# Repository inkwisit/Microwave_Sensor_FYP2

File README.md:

# Microwave_Sensor_FYP2
My final year project on subject of microwave sensors for industrial and robotics use. In an attempt to learn practical aspects of microwave theory, high frequency effects on circuit design, miniature radar and antennas we are recreating MIT Lincoln Lab synthetic aperture radar using own modules.

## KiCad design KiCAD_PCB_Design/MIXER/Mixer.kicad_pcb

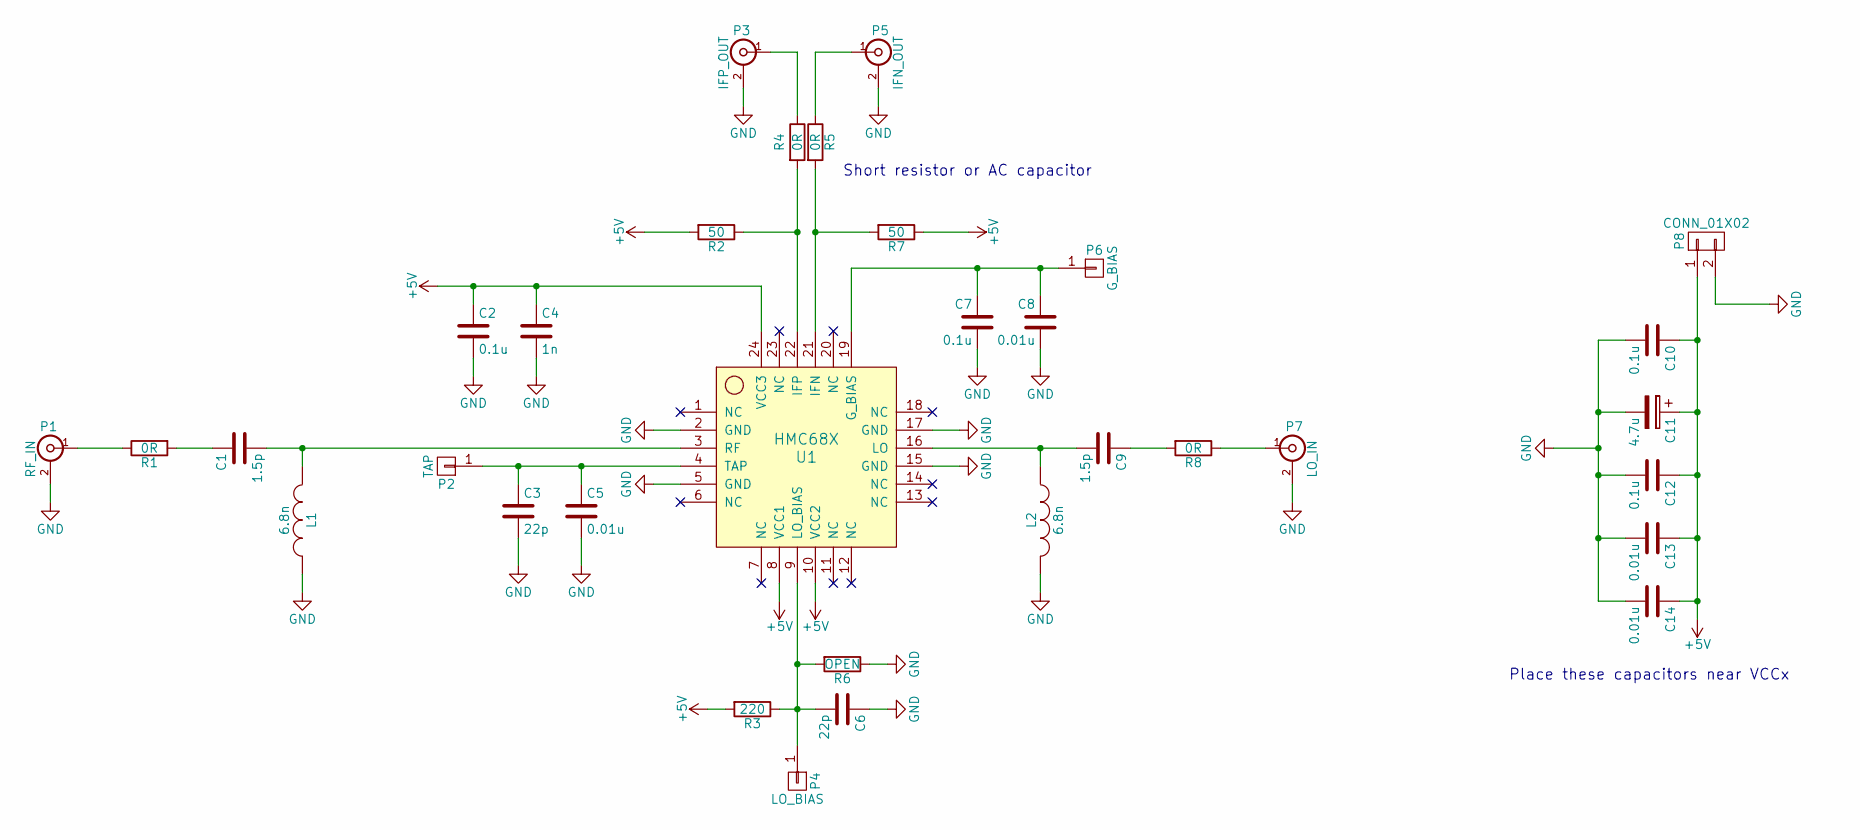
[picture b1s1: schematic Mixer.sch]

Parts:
C1, C9: 1.5p; C_0805_HandSoldering
C2, C7, C10, C12: 0.1u; C_0805_HandSoldering
C3, C6: 22p; C_0805_HandSoldering
C4: 1n; C_0805_HandSoldering
C5, C8, C13, C14: 0.01u; C_0805_HandSoldering
C11: 4.7u; TantalC_SizeA_EIA-3216_Reflow
L1, L2: 6.8n; R_0603_HandSoldering
P1: RF_IN; SMA
P2: TAP; Pin_Header_Straight_1x01
P3: IFP_OUT; SMA
P4: LO_BIAS; Pin_Header_Straight_1x01
P5: IFN_OUT; SMA
P6: G_BIAS; Pin_Header_Straight_1x01
P7: LO_IN; SMA
P8: CONN_01X02; Pin_Header_Straight_1x02
R1, R4, R5, R8: 0R; R_0805_HandSoldering
R2, R7: 50; R_0805_HandSoldering
R3: 220; R_0805_HandSoldering
R6: OPEN; R_0805_HandSoldering
U1: HMC68X; QFN-24-1EP_4x4mm_Pitch0.5mm

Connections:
+5V: C2.1, C4.1, C10.1, C11.1, C12.1, C13.1, C14.1, P8.1, R2.2, R3.2, R7.1, U1.8 (VCC1), U1.10 (VCC2), U1.24 (VCC3)
GND: C2.2, C3.2, C4.2, C5.2, C6.1, C7.2, C8.2, C10.2, C11.2, C12.2, C13.2, C14.2, L1.2, L2.2, P1.2 (Ext), P3.2 (Ext), P5.2 (Ext), P7.2 (Ext), P8.2, R6.1, U1.2 (GND), U1.5 (GND), U1.15 (GND), U1.17 (GND)
unnamed: C1.1, R1.2
unnamed: C1.2, L1.1, U1.3 (RF)
unnamed: C3.1, C5.1, P2.1, U1.4 (TAP)
unnamed: C6.2, P4.1, R3.1, R6.2, U1.9 (LO_BIAS)
unnamed: C7.1, C8.1, P6.1, U1.19 (G_BIAS)
unnamed: C9.1, R8.2
unnamed: C9.2, L2.1, U1.16 (LO)
unnamed: P1.1 (In), R1.1
unnamed: P3.1 (In), R4.1
unnamed: P5.1 (In), R5.1
unnamed: P7.1 (In), R8.1
unnamed: R2.1, R4.2, U1.22 (IFP)
unnamed: R5.2, R7.2, U1.21 (IFN)

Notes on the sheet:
Short resistor or AC capacitor
Place these capacitors near VCCx

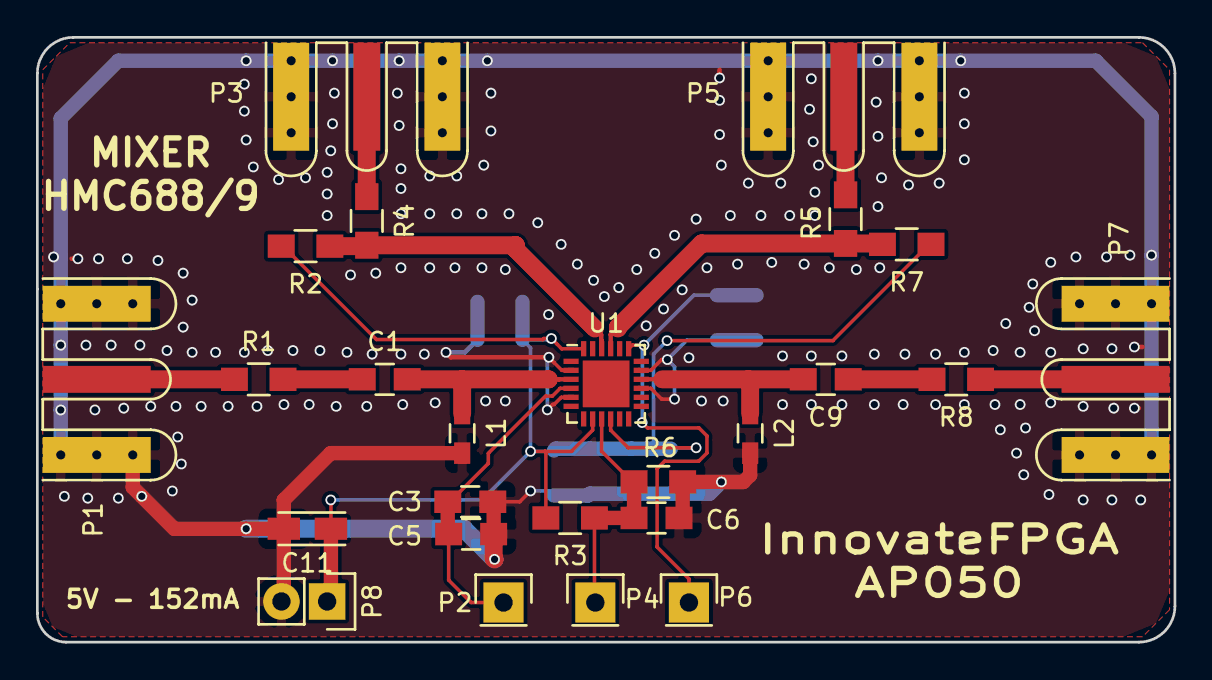
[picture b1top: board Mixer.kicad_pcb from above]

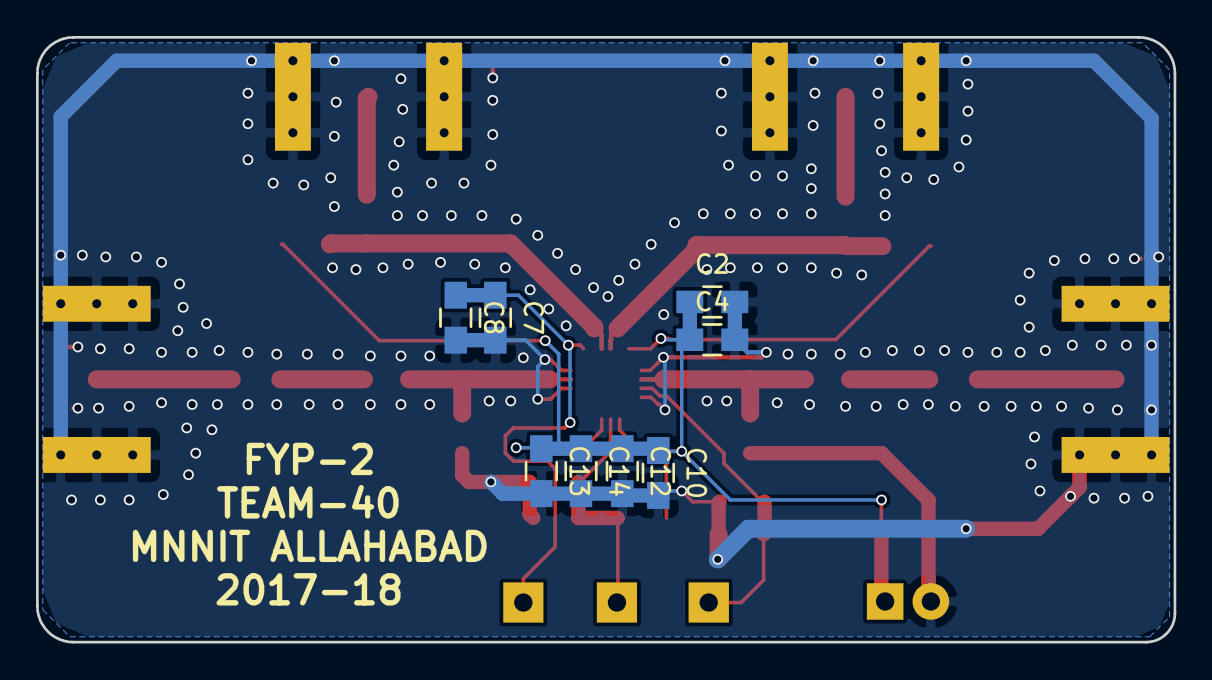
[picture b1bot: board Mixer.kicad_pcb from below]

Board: 2 copper layers, 63.2 x 33.6 mm, 33 parts (8 on the bottom side), 15 nets.

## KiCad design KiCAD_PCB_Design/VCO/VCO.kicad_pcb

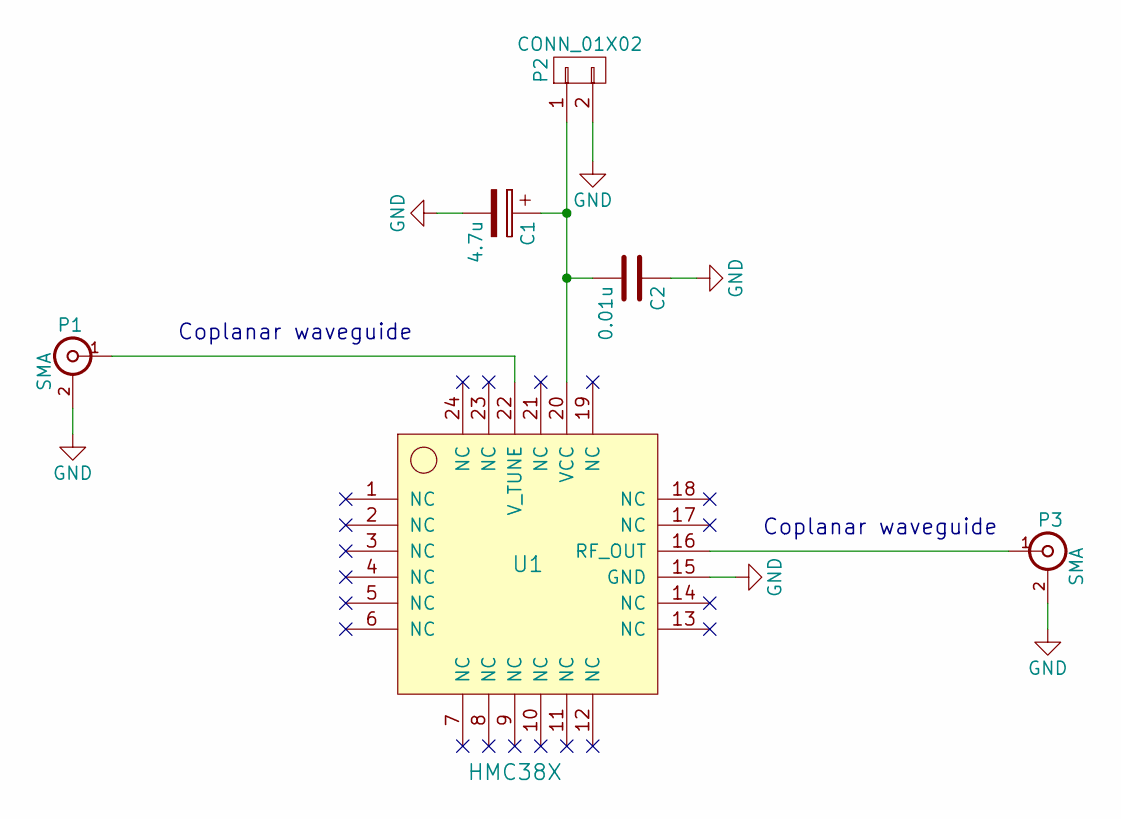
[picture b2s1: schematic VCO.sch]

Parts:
C1: 4.7u; TantalC_SizeA_EIA-3216_Wave
C2: 0.01u; C_0805_HandSoldering
P1, P3: SMA
P2: CONN_01X02; Pin_Header_Straight_1x02
U1: HMC38X; QFN-24-1EP_4x4mm_Pitch0.5mm

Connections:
GND: C1.2, C2.1, P1.2 (Ext), P2.2, P3.2 (Ext), U1.15 (GND)
unnamed: C1.1, C2.2, P2.1, U1.20 (VCC)
unnamed: P1.1 (In), U1.22 (V_TUNE)
unnamed: P3.1 (In), U1.16 (RF_OUT)

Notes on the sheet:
Coplanar waveguide

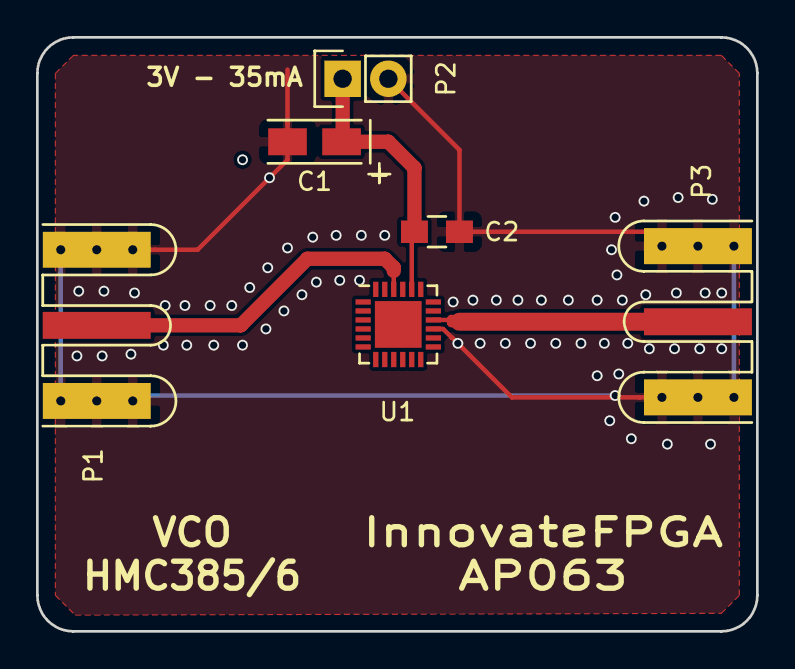
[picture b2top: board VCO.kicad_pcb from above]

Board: 2 copper layers, 40.0 x 33.0 mm, 6 parts (0 on the bottom side), 4 nets.

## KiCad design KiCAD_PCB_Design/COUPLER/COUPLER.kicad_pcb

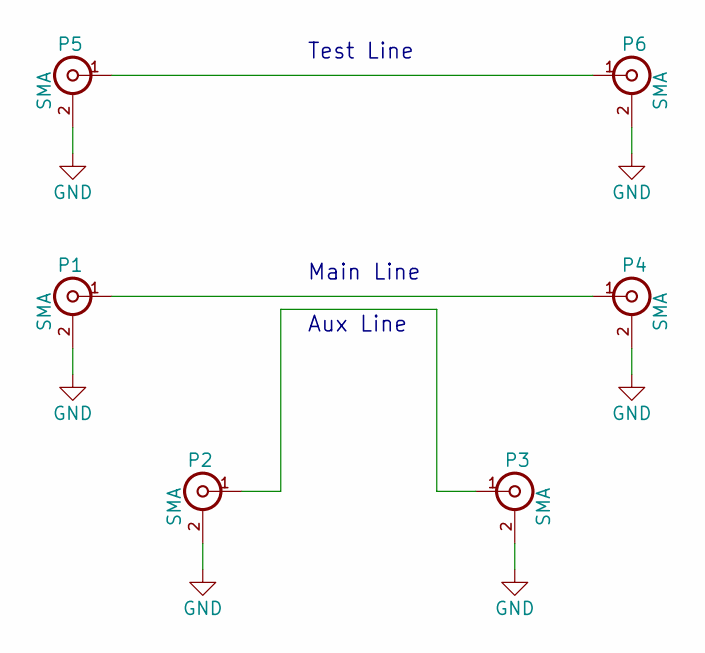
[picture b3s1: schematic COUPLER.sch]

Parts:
P1, P2, P3, P4, P5, P6: SMA

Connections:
GND: P1.2 (Ext), P2.2 (Ext), P3.2 (Ext), P4.2 (Ext), P5.2 (Ext), P6.2 (Ext)
unnamed: P1.1 (In), P4.1 (In)
unnamed: P2.1 (In), P3.1 (In)
unnamed: P5.1 (In), P6.1 (In)

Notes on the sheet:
Main Line
Aux Line
Test Line

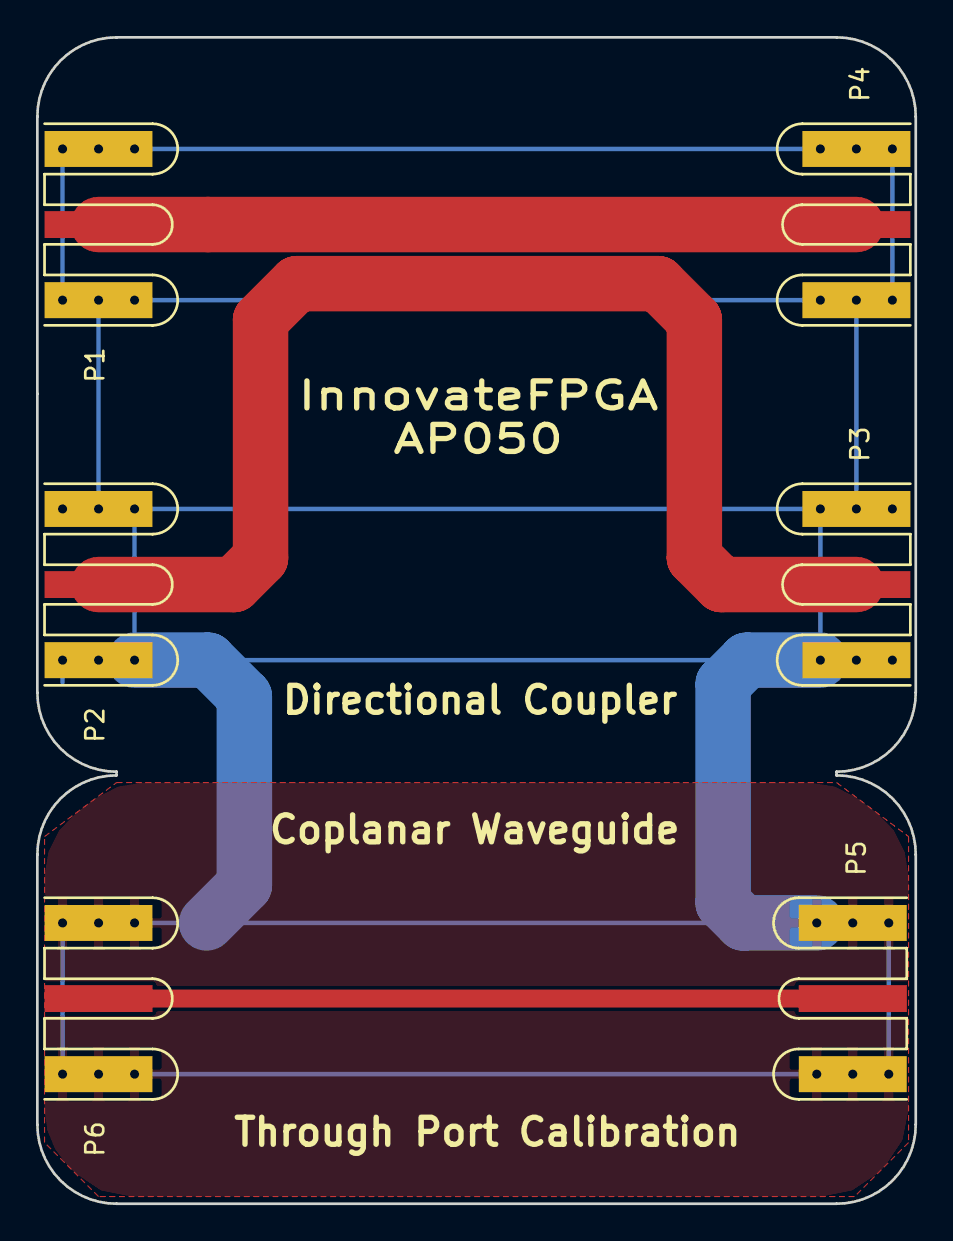
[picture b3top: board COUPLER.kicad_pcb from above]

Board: 2 copper layers, 48.8 x 64.8 mm, 6 parts (0 on the bottom side), 4 nets.

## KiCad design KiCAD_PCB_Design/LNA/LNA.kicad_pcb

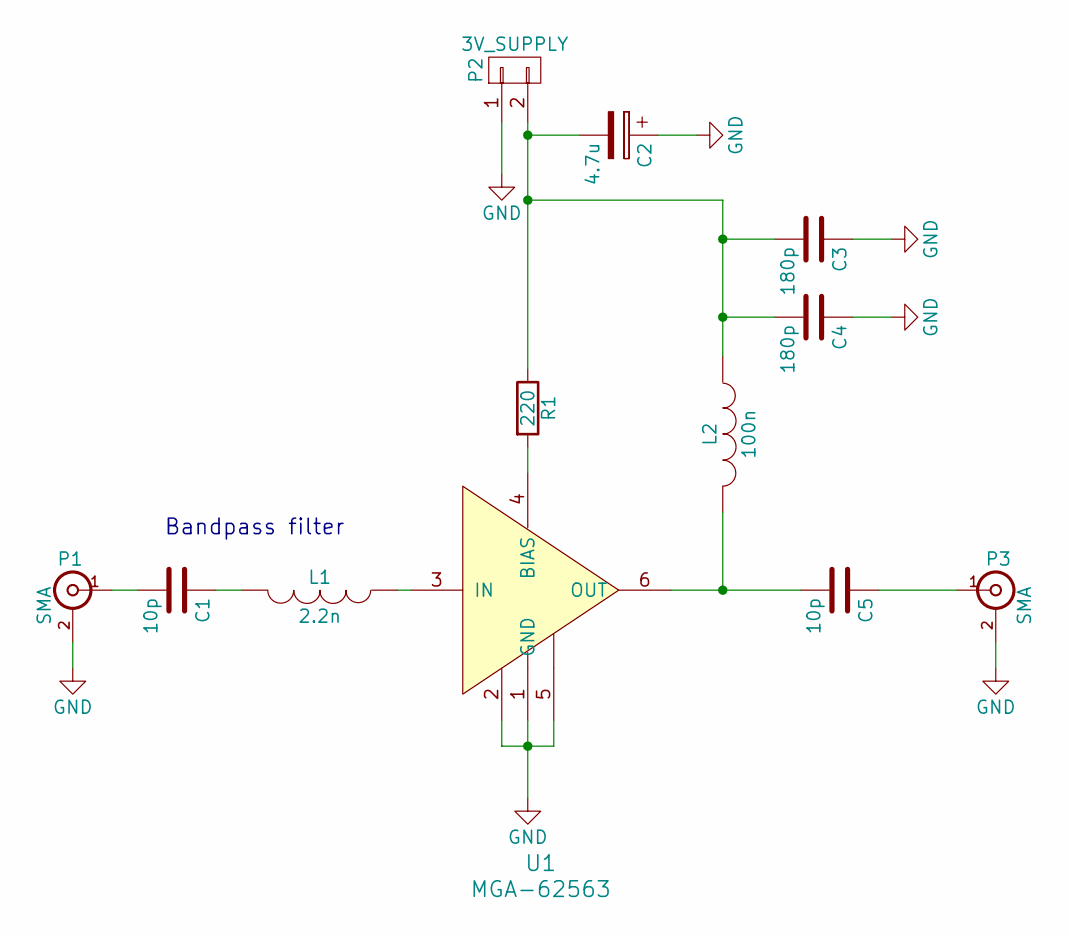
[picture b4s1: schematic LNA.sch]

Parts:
C1, C5: 10p; C_0805_HandSoldering
C2: 4.7u; TantalC_SizeA_EIA-3216_Wave
C3, C4: 180p; C_0805_HandSoldering
L1: 2.2n; R_0805_HandSoldering
L2: 100n; R_0805_HandSoldering
P1, P3: SMA
P2: 3V_SUPPLY; Pin_Header_Straight_1x02
R1: 220; R_0805_HandSoldering
U1: MGA-62563; SOT-363

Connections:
GND: C2.1, C3.1, C4.1, P1.2 (Ext), P2.1, P3.2 (Ext), U1.1 (GND), U1.2, U1.5
unnamed: C1.1, L1.2
unnamed: C1.2, P1.1 (In)
unnamed: C2.2, C3.2, C4.2, L2.1, P2.2, R1.1
unnamed: C5.1, P3.1 (In)
unnamed: C5.2, L2.2, U1.6 (OUT)
unnamed: L1.1, U1.3 (IN)
unnamed: R1.2, U1.4 (BIAS)

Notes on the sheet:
Bandpass filter

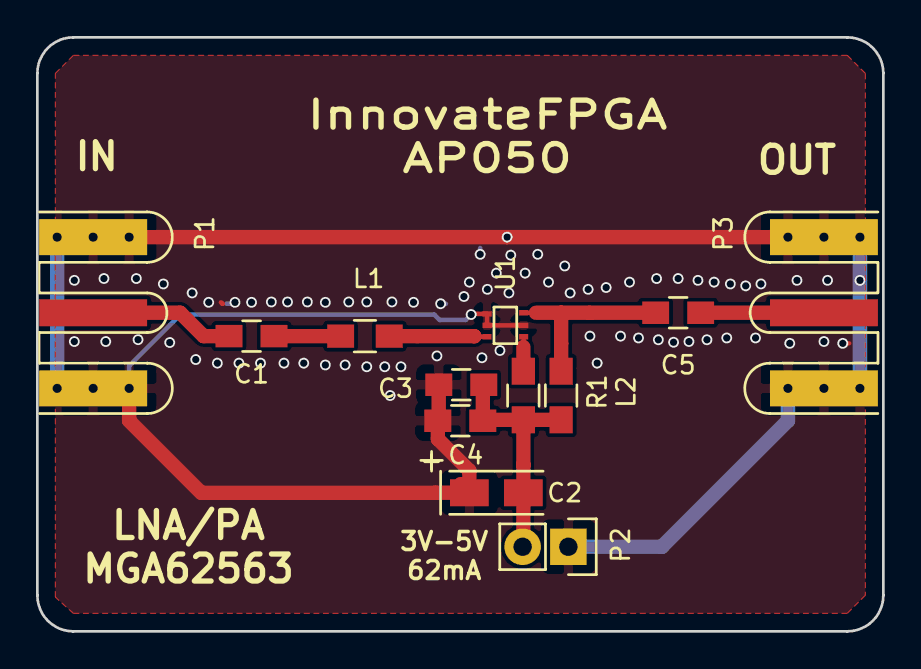
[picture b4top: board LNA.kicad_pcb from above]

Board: 2 copper layers, 47.0 x 33.0 mm, 12 parts (0 on the bottom side), 8 nets.

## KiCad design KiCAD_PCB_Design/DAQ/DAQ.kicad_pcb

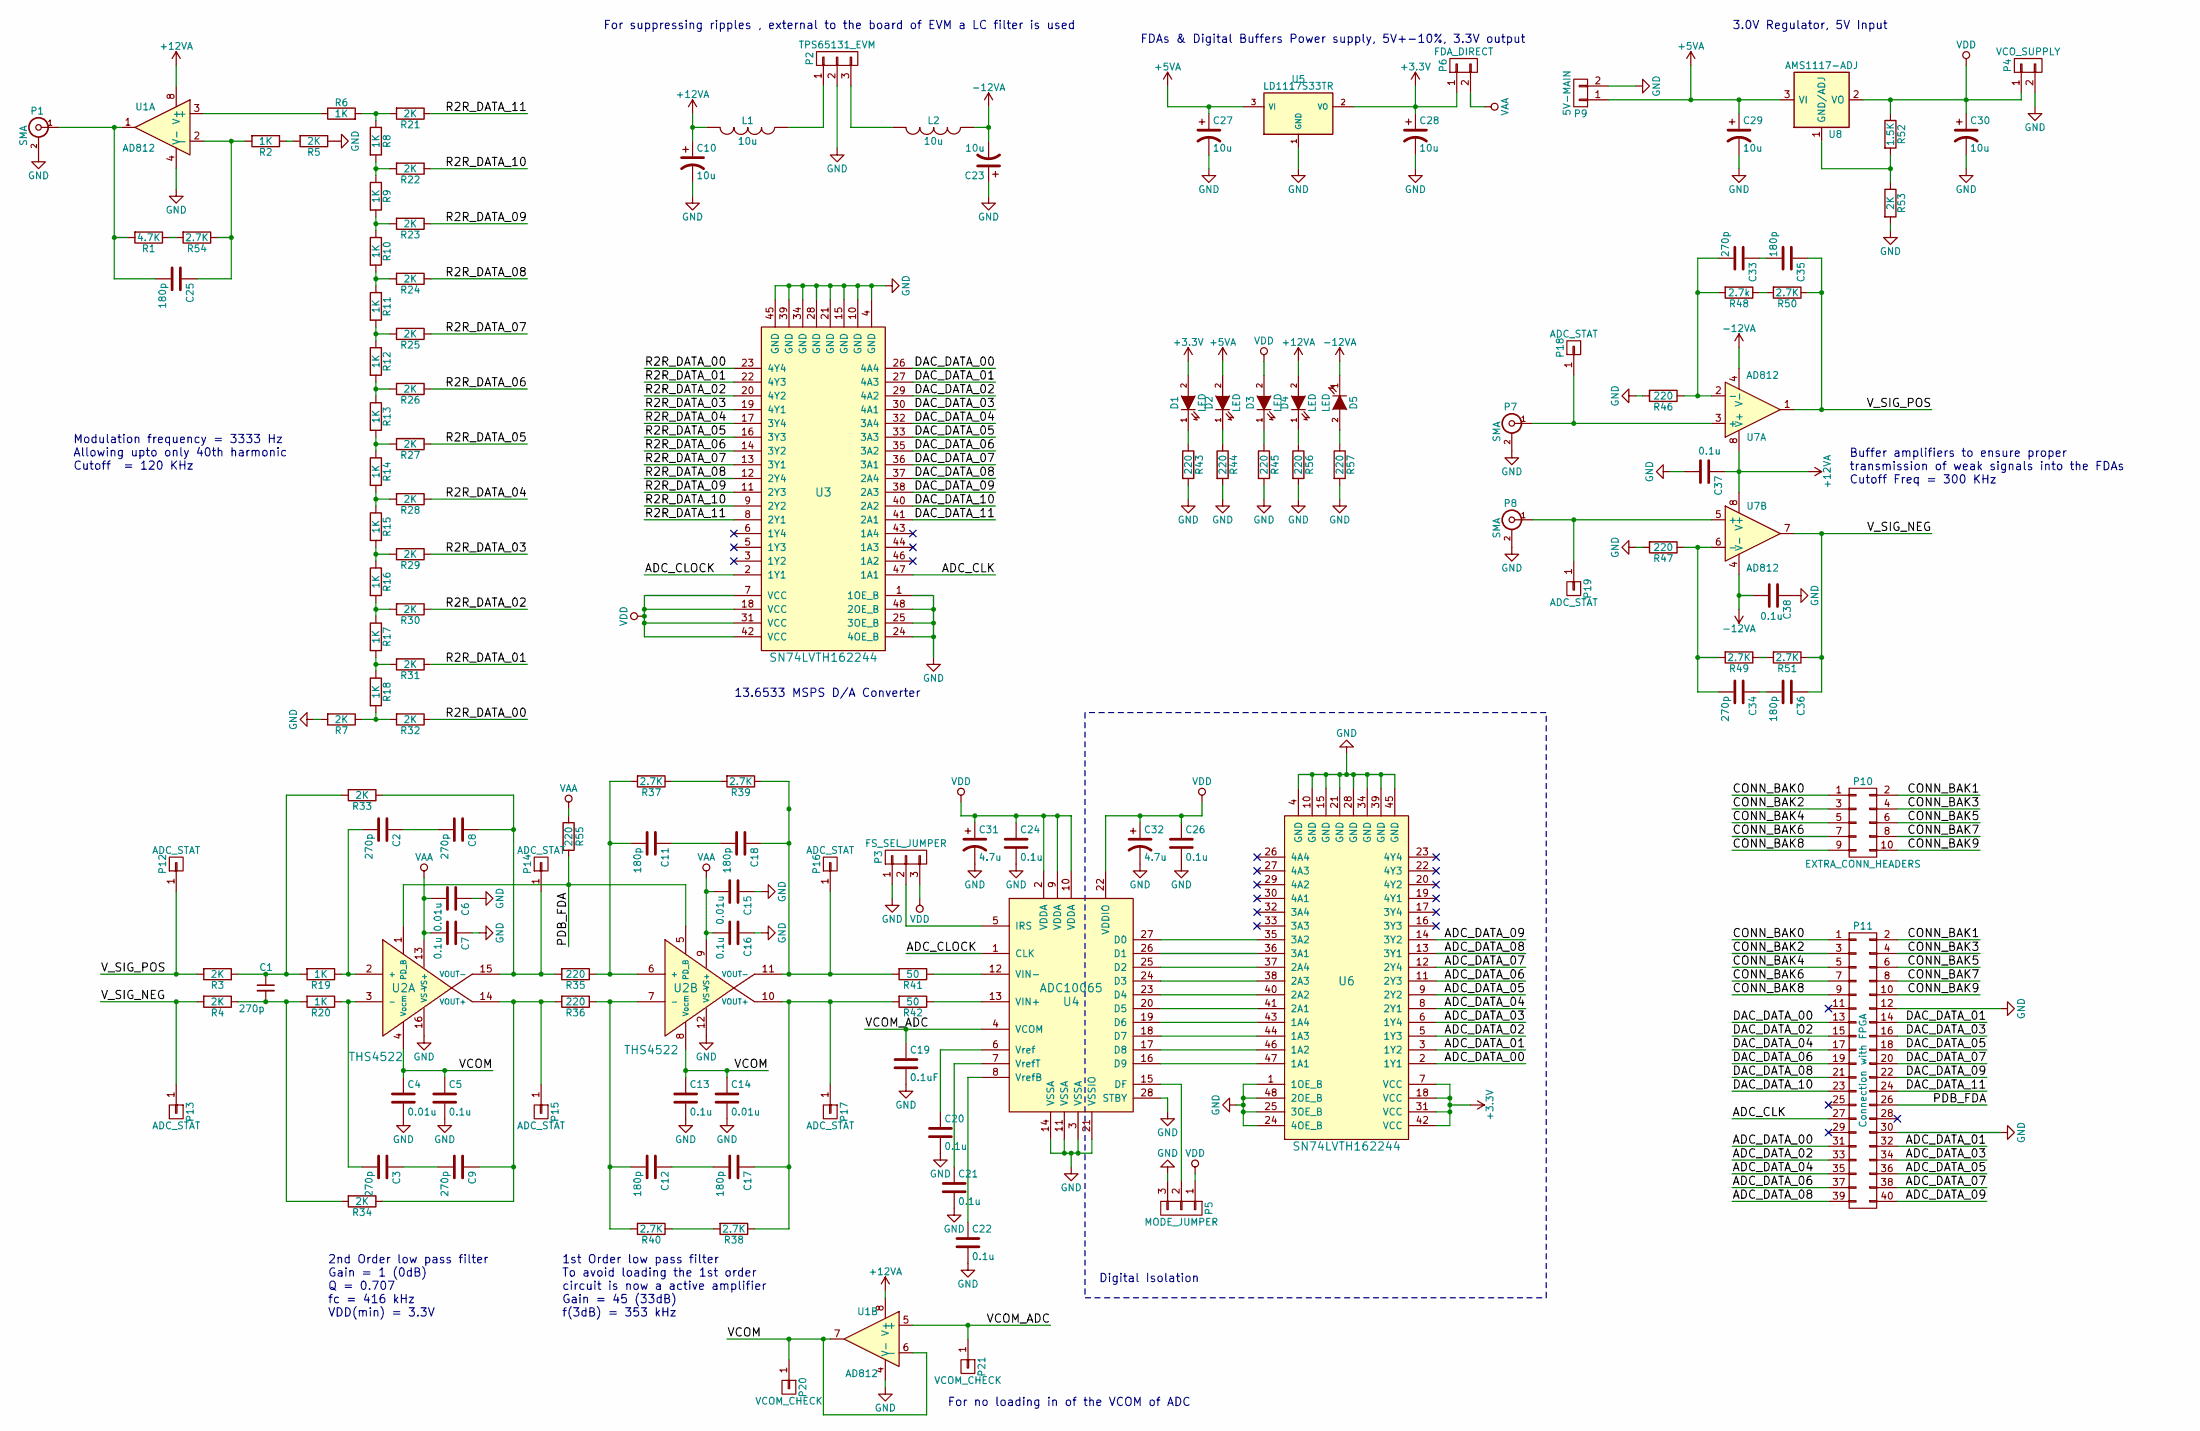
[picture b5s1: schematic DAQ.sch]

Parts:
C1, C2, C3, C8, C9, C33, C34: 270p; C_0805_HandSoldering
C4, C6, C14, C15: 0.01u; C_0805_HandSoldering
C5, C7, C13, C16, C20, C21, C22, C24, C26, C37, C38: 0.1u; C_0805_HandSoldering
C10, C23, C29, C30: 10u; c_elec_3x5.3
C11, C12, C17, C18, C25, C35, C36: 180p; C_0805_HandSoldering
C19: 0.1uF; C_0805_HandSoldering
C27, C28: 10u; TantalC_SizeS_EIA-3216
C31, C32: 4.7u; TantalC_SizeS_EIA-3216
D1, D2, D3, D4, D5: LED; LED_0805
L1, L2: 10u; Bourns_Semi_Shielded_Power_Inductor_SRN5040
P1, P7, P8: SMA
P2: TPS65131_EVM; Pin_Header_Straight_1x03
P3: FS_SEL_JUMPER; Pin_Header_Straight_1x03
P4: VCO_SUPPLY; Pin_Header_Straight_1x02
P5: MODE_JUMPER; Pin_Header_Straight_1x03
P6: FDA_DIRECT; Pin_Header_Straight_1x02
P9: 5V-MAIN; Pin_Header_Straight_1x02
P10: EXTRA_CONN_HEADERS; Pin_Header_Straight_2x05
P11: Connection with FPGA; Pin_Header_Straight_2x20
P12, P13, P14, P15, P16, P17, P18, P19: ADC_STAT; Pin_Header_Straight_1x01
P20, P21: VCOM_CHECK; Pin_Header_Straight_1x01
R1: 4.7K; R_0805_HandSoldering
R2, R6, R8, R9, R10, R11, R12, R13, R14, R15, R16, R17, R18, R19, R20: 1K; R_0805_HandSoldering
R3, R4, R5, R7, R21, R22, R23, R24, R25, R26, R27, R28, R29, R30, R31, R32, R33, R34, R53: 2K; R_0805_HandSoldering
R35, R36, R43, R44, R45, R46, R47, R55, R56, R57: 220; R_0805_HandSoldering
R37, R38, R39, R40, R49, R50, R51, R54: 2.7K; R_0805_HandSoldering
R41, R42: 50; R_0805_HandSoldering
R48: 2.7k; R_0805_HandSoldering
R52: 1.5K; R_0805_HandSoldering
U1, U7: AD812; SOIC-8_3.9x4.9mm_Pitch1.27mm
U2: THS4522; TSSOP-16_4.4x5mm_Pitch0.65mm
U3, U6: SN74LVTH162244; TSSOP-48_6.1x12.5mm_Pitch0.5mm
U4: ADC10065; TSSOP-28_4.4x9.7mm_Pitch0.65mm
U5: LD1117S33TR; SOT-223
U8: AMS1117-ADJ; SOT-223

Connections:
+3V3: C28.1, D1.2 (A), P6.1, U5.2 (VO), U6.7 (VCC), U6.18 (VCC), U6.31 (VCC), U6.42 (VCC)
+5VA: C27.1, C29.1, D2.2 (A), P9.1, U5.3 (VI), U8.3 (VI)
+12VA: C10.1, C37.1, D4.2 (A), L1.2, U1.8 (V+), U7.8 (V+)
-12VA: C23.2, C38.2, D5.1 (K), L2.1, U7.4 (V-)
/ADC_CLK: P11.27, U3.47 (1A1)
/ADC_CLOCK: U3.2 (1Y1), U4.1 (CLK)
/ADC_DATA_00: P11.31, U6.2 (1Y1)
/ADC_DATA_01: P11.32, U6.3 (1Y2)
/ADC_DATA_02: P11.33, U6.5 (1Y3)
/ADC_DATA_03: P11.34, U6.6 (1Y4)
/ADC_DATA_04: P11.35, U6.8 (2Y1)
/ADC_DATA_05: P11.36, U6.9 (2Y2)
/ADC_DATA_06: P11.37, U6.11 (2Y3)
/ADC_DATA_07: P11.38, U6.12 (2Y4)
/ADC_DATA_08: P11.39, U6.13 (3Y1)
/ADC_DATA_09: P11.40, U6.14 (3Y2)
/CONN_BAK0: P10.1, P11.1
/CONN_BAK1: P10.2, P11.2
/CONN_BAK2: P10.3, P11.3
/CONN_BAK3: P10.4, P11.4
/CONN_BAK4: P10.5, P11.5
/CONN_BAK5: P10.6, P11.6
/CONN_BAK6: P10.7, P11.7
/CONN_BAK7: P10.8, P11.8
/CONN_BAK8: P10.9, P11.9
/CONN_BAK9: P10.10, P11.10
/DAC_DATA_00: P11.13, U3.26 (4A4)
/DAC_DATA_01: P11.14, U3.27 (4A3)
/DAC_DATA_02: P11.15, U3.29 (4A2)
/DAC_DATA_03: P11.16, U3.30 (4A1)
/DAC_DATA_04: P11.17, U3.32 (3A4)
/DAC_DATA_05: P11.18, U3.33 (3A3)
/DAC_DATA_06: P11.19, U3.35 (3A2)
/DAC_DATA_07: P11.20, U3.36 (3A1)
/DAC_DATA_08: P11.21, U3.37 (2A4)
/DAC_DATA_09: P11.22, U3.38 (2A3)
/DAC_DATA_10: P11.23, U3.40 (2A2)
/DAC_DATA_11: P11.24, U3.41 (2A1)
/PDB_FDA: P11.26, R55.2, U2.1 (PD_B), U2.5 (PD_B)
/R2R_DATA_00: R32.1, U3.23 (4Y4)
/R2R_DATA_01: R31.1, U3.22 (4Y3)
/R2R_DATA_02: R30.1, U3.20 (4Y2)
/R2R_DATA_03: R29.1, U3.19 (4Y1)
/R2R_DATA_04: R28.1, U3.17 (3Y4)
/R2R_DATA_05: R27.1, U3.16 (3Y3)
/R2R_DATA_06: R26.1, U3.14 (3Y2)
/R2R_DATA_07: R25.1, U3.13 (3Y1)
/R2R_DATA_08: R24.1, U3.12 (2Y4)
/R2R_DATA_09: R23.1, U3.11 (2Y3)
/R2R_DATA_10: R22.1, U3.9 (2Y2)
/R2R_DATA_11: R21.1, U3.8 (2Y1)
/VCOM: C4.1, C5.1, C13.1, C14.1, P20.1, U1.6 (-), U1.7, U2.4 (Vocm), U2.8 (Vocm)
/VCOM_ADC: C19.1, P21.1, U1.5 (+), U4.4 (VCOM)
/V_SIG_NEG: C36.1, P13.1, R4.2, R51.1, U7.7
/V_SIG_POS: C35.1, P12.1, R3.2, R50.1, U7.1
GND: C4.2, C5.2, C6.1, C7.1, C10.2, C13.2, C14.2, C15.1, C16.1, C19.2, C20.2, C21.2, C22.2, C23.1, C24.2, C26.2, C27.2, C28.2, C29.2, C30.2, C31.2, C32.2, C37.2, C38.1, P1.2 (Ext), P2.2, P3.1, P4.2, P5.3, P7.2 (Ext), P8.2 (Ext), P9.2, P11.12, P11.30, R5.1, R7.2, R43.2, R44.2, R45.2, R46.2, R47.2, R53.2, R56.2, R57.2, U1.4 (V-), U2.12 (VS-), U2.16 (VS-), U3.1 (1OE_B), U3.4 (GND), U3.10 (GND), U3.15 (GND), U3.21 (GND), U3.24 (4OE_B), U3.25 (3OE_B), U3.28 (GND), U3.34 (GND), U3.39 (GND), U3.45 (GND), U3.48 (2OE_B), U4.3 (VSSA), U4.11 (VSSA), U4.14 (VSSA), U4.21 (VSSIO), U4.28 (STBY), U5.1 (GND), U6.1 (1OE_B), U6.4 (GND), U6.10 (GND), U6.15 (GND), U6.21 (GND), U6.24 (4OE_B), U6.25 (3OE_B), U6.28 (GND), U6.34 (GND), U6.39 (GND), U6.45 (GND), U6.48 (2OE_B)
unnamed: C1.1, R3.1, R19.2, R33.2
unnamed: C1.2, R4.1, R20.2, R34.2
unnamed: C2.1, C8.2
unnamed: C2.2, R19.1, U2.2 (+)
unnamed: C3.1, C9.2
unnamed: C3.2, R20.1, U2.3 (-)
unnamed: C8.1, P14.1, R33.1, R35.2, U2.15 (VOUT-)
unnamed: C9.1, P15.1, R34.1, R36.2, U2.14 (VOUT+)
unnamed: C11.1, C18.2
unnamed: C11.2, R35.1, R37.2, U2.6 (+)
unnamed: C12.1, C17.2
unnamed: C12.2, R36.1, R40.2, U2.7 (-)
unnamed: C17.1, P17.1, R38.1, R42.2, U2.10 (VOUT+)
unnamed: C18.1, P16.1, R39.1, R41.2, U2.11 (VOUT-)
unnamed: C20.1, U4.6 (Vref)
unnamed: C21.1, U4.7 (VrefT)
unnamed: C22.1, U4.8 (VrefB)
unnamed: C25.1, R2.2, R54.1, U1.2 (-)
unnamed: C25.2, P1.1 (In), R1.2, U1.1
unnamed: C33.1, C35.2
unnamed: C33.2, R46.1, R48.2, U7.2 (-)
unnamed: C34.1, C36.2
unnamed: C34.2, R47.1, R49.2, U7.6 (-)
unnamed: D1.1 (K), R43.1
unnamed: D2.1 (K), R44.1
unnamed: D3.1 (K), R45.1
unnamed: D4.1 (K), R56.1
unnamed: D5.2 (A), R57.1
unnamed: L1.1, P2.1
unnamed: L2.2, P2.3
unnamed: P3.2, U4.5 (IRS)
unnamed: P5.2, U4.15 (DF)
unnamed: P7.1 (In), P18.1, U7.3 (+)
unnamed: P8.1 (In), P19.1, U7.5 (+)
unnamed: R1.1, R54.2
unnamed: R2.1, R5.2
unnamed: R6.1, U1.3 (+)
unnamed: R9.2, R10.1, R23.2
unnamed: R10.2, R11.1, R24.2
unnamed: R11.2, R12.1, R25.2
unnamed: R12.2, R13.1, R26.2
unnamed: R13.2, R14.1, R27.2
unnamed: R14.2, R15.1, R28.2
unnamed: R15.2, R16.1, R29.2
unnamed: R16.2, R17.1, R30.2
unnamed: R17.2, R18.1, R31.2
unnamed: R7.1, R18.2, R32.2
unnamed: R6.2, R8.1, R21.2
unnamed: R8.2, R9.1, R22.2
unnamed: R37.1, R39.2
unnamed: R38.2, R40.1
unnamed: R41.1, U4.12 (VIN-)
unnamed: R42.1, U4.13 (VIN+)
unnamed: R48.1, R50.2
unnamed: R49.1, R51.2
unnamed: R52.2, R53.1, U8.1 (GND/ADJ)
unnamed: U4.16 (D9), U6.47 (1A1)
unnamed: U4.17 (D8), U6.46 (1A2)
unnamed: U4.18 (D7), U6.44 (1A3)
unnamed: U4.19 (D6), U6.43 (1A4)
unnamed: U4.20 (D5), U6.41 (2A1)
unnamed: U4.23 (D4), U6.40 (2A2)
unnamed: U4.24 (D3), U6.38 (2A3)
unnamed: U4.25 (D2), U6.37 (2A4)
unnamed: U4.26 (D1), U6.36 (3A1)
unnamed: U4.27 (D0), U6.35 (3A2)
VAA: C6.2, C7.2, C15.2, C16.2, P6.2, R55.1, U2.9 (VS+), U2.13 (VS+)
VDD: C24.1, C26.1, C30.1, C31.1, C32.1, D3.2 (A), P3.3, P4.1, P5.1, R52.1, U3.7 (VCC), U3.18 (VCC), U3.31 (VCC), U3.42 (VCC), U4.2 (VDDA), U4.9 (VDDA), U4.10 (VDDA), U4.22 (VDDIO), U8.2 (VO)

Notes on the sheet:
3.0V Regulator, 5V Input
Digital Isolation
FDAs & Digital Buffers Power supply, 5V+-10%, 3.3V output
1st Order low pass filter To avoid loading the 1st order circuit is now a active amplifier Gain = 45 (33dB) f(3dB) = 353 kHz
2nd Order low pass filter Gain = 1 (0dB) Q = 0.707 fc = 416 kHz VDD(min) = 3.3V
For suppressing ripples , external to the board of EVM a LC filter is used
Buffer amplifiers to ensure proper transmission of weak signals into the FDAs Cutoff Freq = 300 KHz
Modulation frequency = 3333 Hz Allowing upto only 40th harmonic Cutoff = 120 KHz
13.6533 MSPS D/A Converter
For no loading in of the VCOM of ADC

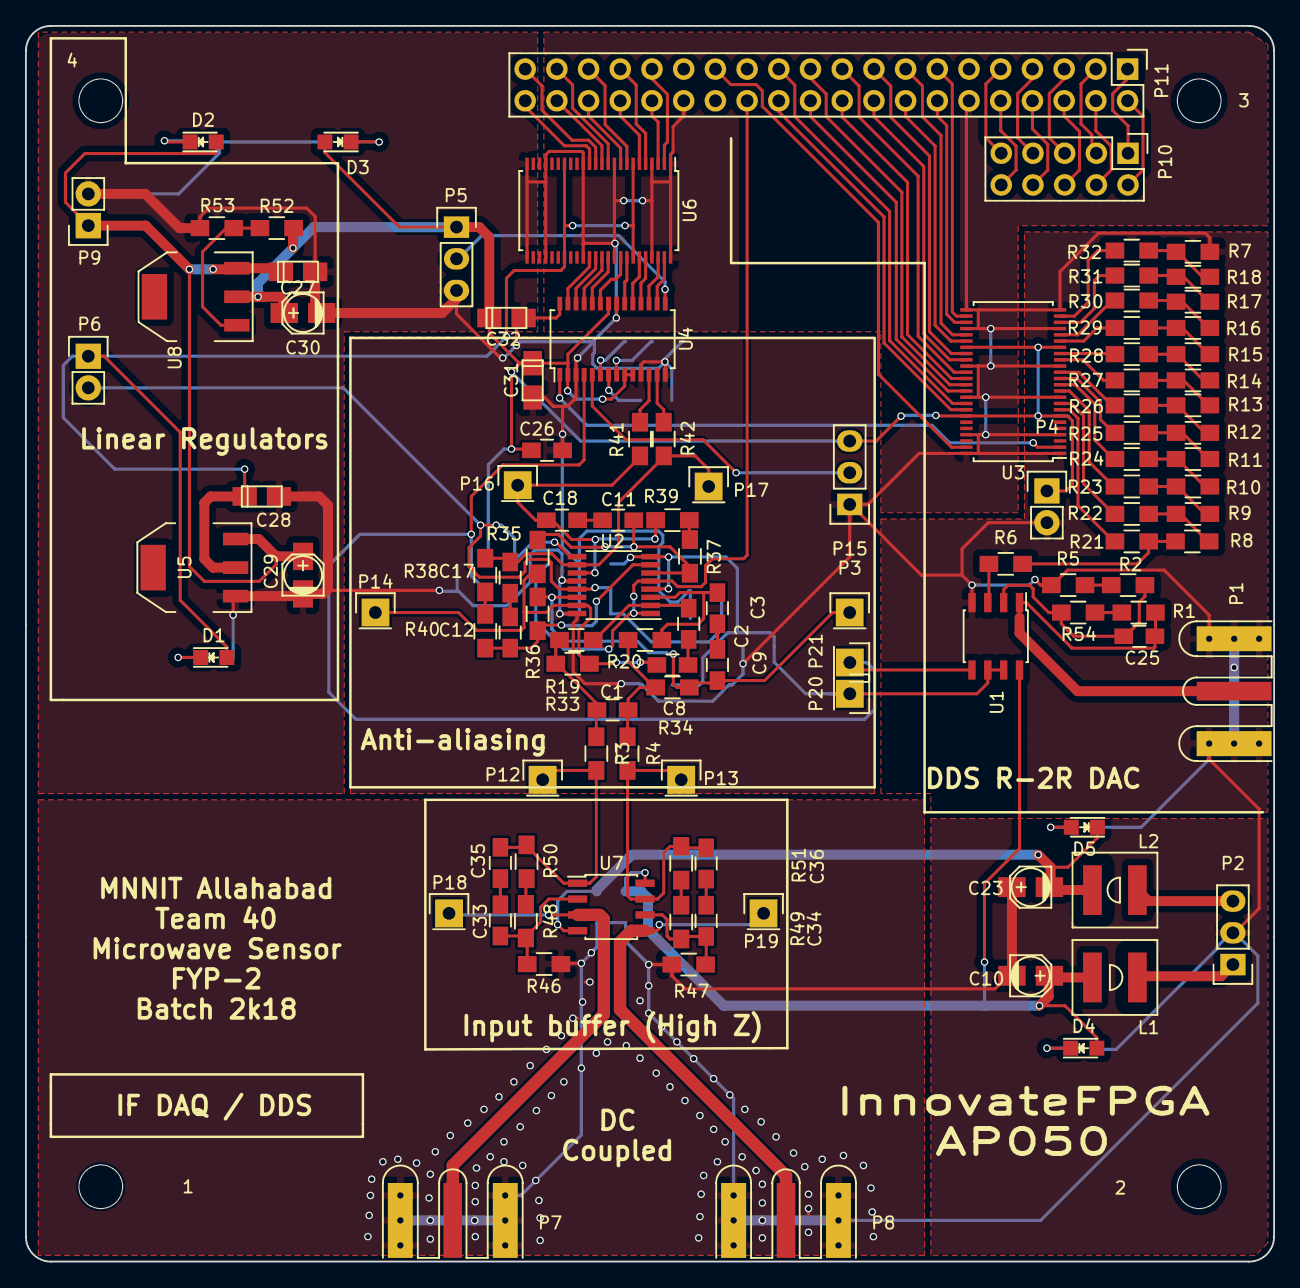
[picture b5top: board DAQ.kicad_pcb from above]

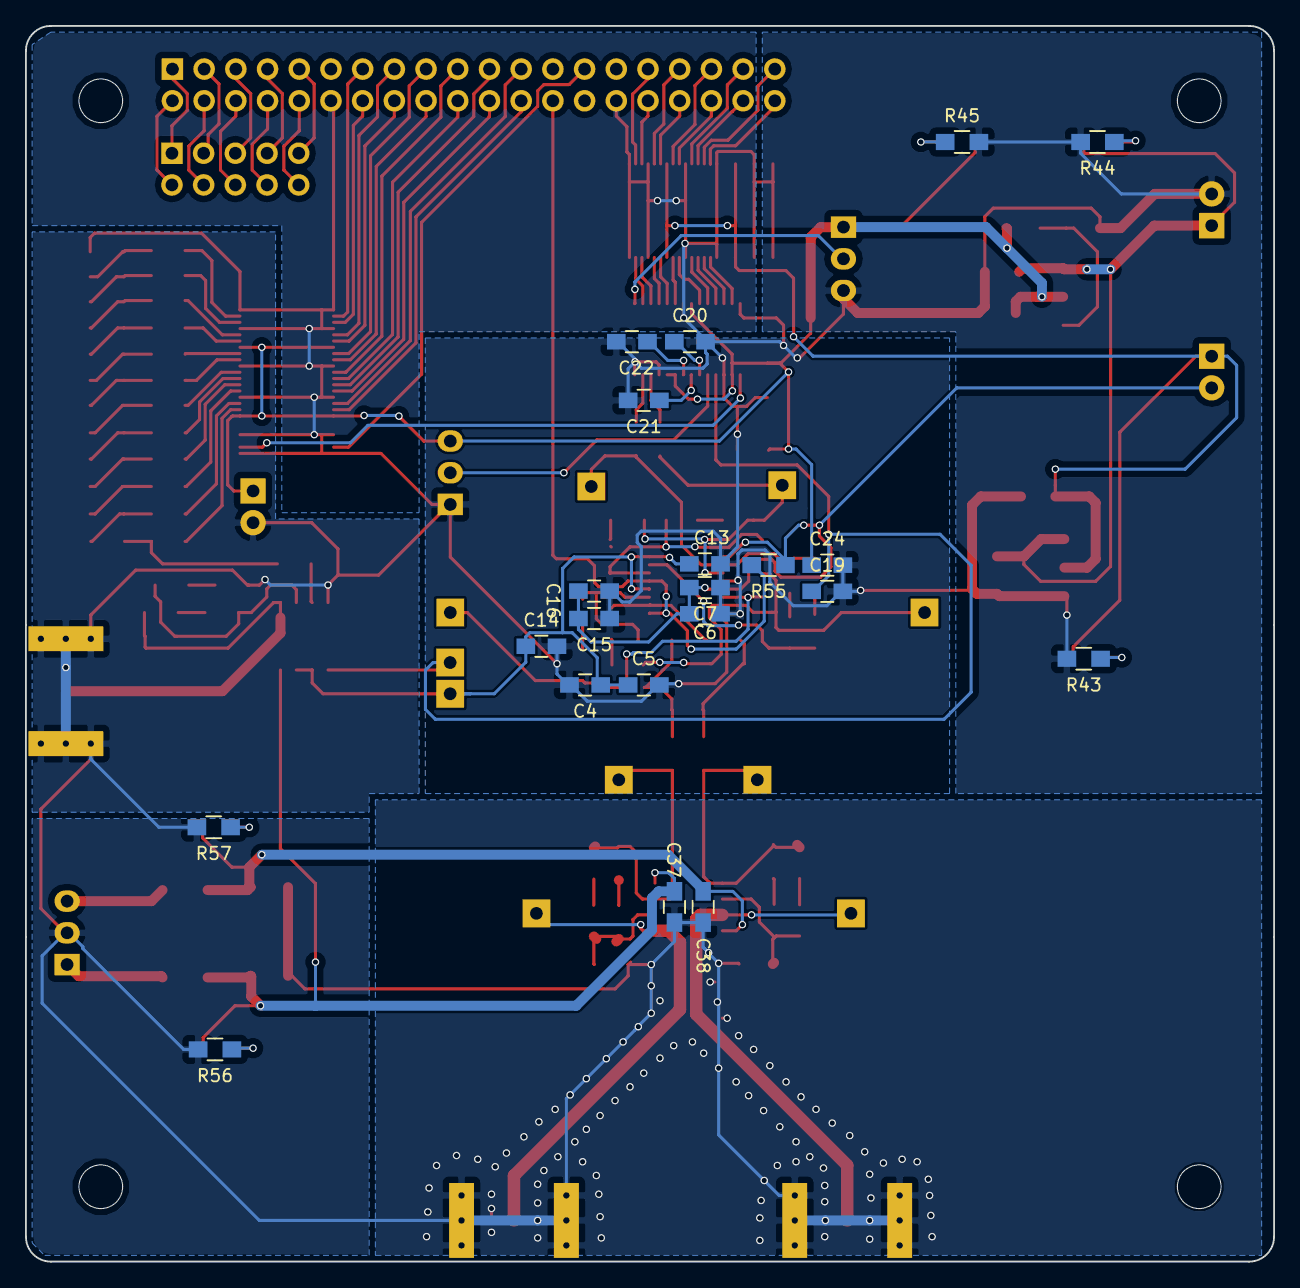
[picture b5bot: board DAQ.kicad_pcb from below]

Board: 2 copper layers, 100.0 x 99.0 mm, 135 parts (21 on the bottom side), 124 nets.

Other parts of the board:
1, 2, 3, 4: MountingHole_3-5mm

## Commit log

2018-03-15 First commit : Component selection started
2018-03-17 Mini-circuits appnote added
2018-03-24 Added library parts & started schematic designing
2018-03-28 Schematic of DAQ.sch is almost complete, Making footprints of SMA, learning about patch array antennas
2018-03-30 Routing of the PCB is complete, Now procedding towards zone fills
2018-03-31 VCO PCB design complete, ongoing LNA & PA ..
2018-04-07 All components made except antenna, Now verifying ..
